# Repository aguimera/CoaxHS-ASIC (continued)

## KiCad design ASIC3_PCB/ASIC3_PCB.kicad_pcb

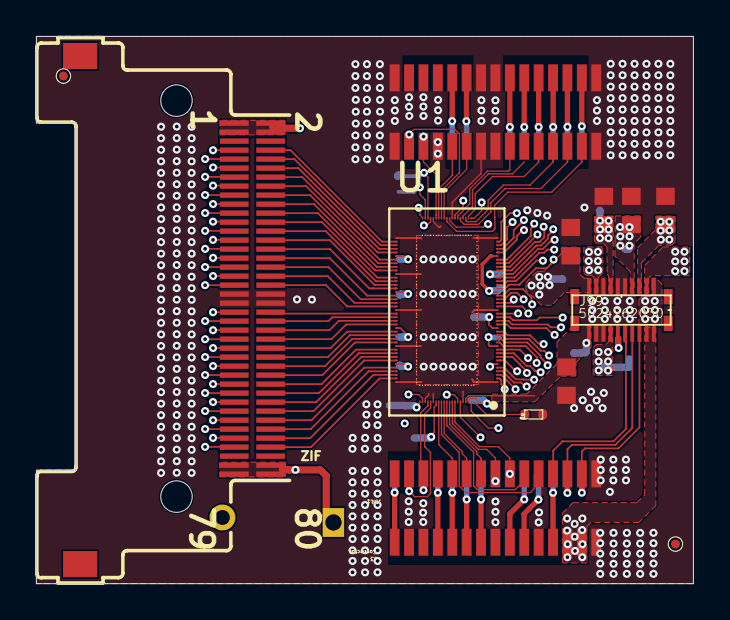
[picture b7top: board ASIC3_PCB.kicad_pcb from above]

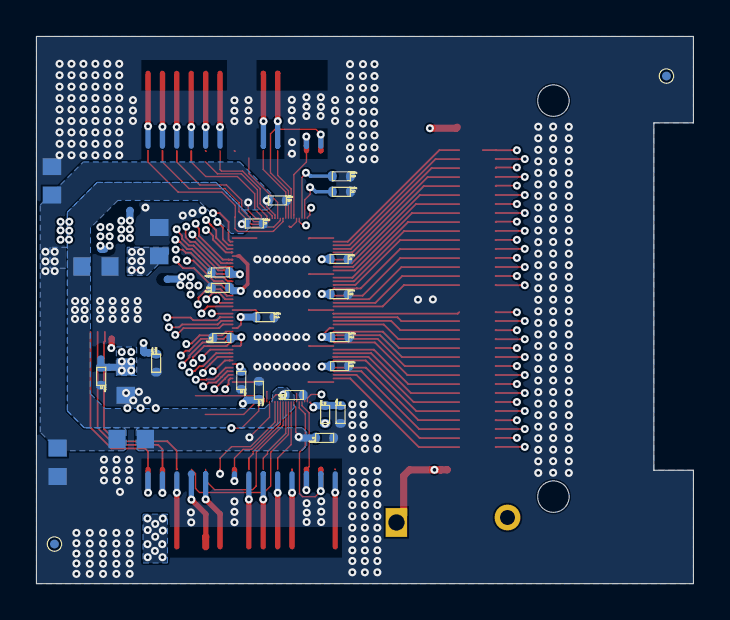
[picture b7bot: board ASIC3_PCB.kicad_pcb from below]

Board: 6 copper layers, 36.5 x 30.4 mm, 42 parts (28 on the bottom side), 101 nets.

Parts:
C1, C2, C4, C5, C6, C7, C8, C9, C10, C11, C12, C13, C14, C17, C18, C19, C400, C401, C402: 100n; C0402
C200, C201, C202, C203, C204, C205, C206, C207, C208, C209: 10uF; CAPC1709X50N
FF1: 0F0; CAPC1709X50N
FID1, FID2, FID3, FID4: FIDUCIAL; MFID0508
J3: Connector; JSIL1THTPad
J6: MOLEX-524653071; J524653071_Board2Board
J11: MEC5-040-01-L-RA-W2-TR
J99: 5024262030; JMOLEX-0559090274V1_pwrcard
J200: MOLEX-524653071; J524653071
R2: 0R0; R0402
R3: 33k; R0402
U1: ASIC3_M; BRAINCOM_ASIC3

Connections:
4V5: J99.2, J99.4, J200.28, J200.29
/Col_0: J11.73 (Col_0), U1.2 (2_VOUT_COL_Q_170)
/Col_1: J11.71 (Col_1), U1.3 (3_VOUT_COL_I_170)
/Col_2: J11.69 (Col_2), U1.4 (4_VOUT_COL_I_180)
/Col_3: J11.67 (Col_3), U1.5 (5_VOUT_COL_Q_180)
/Col_4: J11.65 (Col_4), U1.7 (7_VOUT_COL_Q_190)
/Col_5: J11.63 (Col_5), U1.8 (8_VOUT_COL_I_190)
/Col_6: J11.61 (Col_6), U1.9 (9_VOUT_COL_I_200)
/Col_7: J11.59 (Col_7), U1.10 (10_VOUT_COL_Q_200)
/Col_8: J11.57 (Col_8), U1.12 (12_VOUT_COL_Q_210)
/Col_9: J11.55 (Col_9), U1.13 (13_VOUT_COL_I_210)
/Col_10: J11.53 (Col_10), U1.14 (14_VOUT_COL_I_220)
/Col_11: J11.51 (Col_11), U1.15 (15_VOUT_COL_Q_220)
/Col_12: J11.49 (Col_12), U1.17 (17_VOUT_COL_Q_230)
/Col_13: J11.47 (Col_13), U1.18 (18_VOUT_COL_I_230)
/Col_14: J11.45 (Col_14), U1.19 (19_VOUT_COL_I_240)
/Col_15: J11.43 (Col_15), U1.20 (20_VOUT_COL_Q_240)
/Col_16: J11.37 (Col_16), U1.22 (22_VOUT_COL_Q_250)
/Col_17: J11.35 (Col_17), U1.23 (23_VOUT_COL_I_250)
/Col_18: J11.33 (Col_18), U1.24 (24_VOUT_COL_I_260)
/Col_19: J11.31 (Col_19), U1.25 (25_VOUT_COL_Q_260)
/Col_20: J11.29 (Col_20), U1.27 (27_VOUT_COL_Q_270)
/Col_21: J11.27 (Col_21), U1.28 (28_VOUT_COL_I_270)
/Col_22: J11.25 (Col_22), U1.29 (29_VOUT_COL_I_280)
/Col_23: J11.23 (Col_23), U1.30 (30_VOUT_COL_Q_280)
/Col_24: J11.21 (Col_24), U1.32 (32_VOUT_COL_Q_290)
/Col_25: J11.19 (Col_25), U1.33 (33_VOUT_COL_I_290)
/Col_26: J11.17 (Col_26), U1.34 (34_VOUT_COL_I_300)
/Col_27: J11.15 (Col_27), U1.35 (35_VOUT_COL_Q_300)
/Col_28: J11.13 (Col_28), U1.37 (37_VOUT_COL_Q_310)
/Col_29: J11.11 (Col_29), U1.38 (38_VOUT_COL_I_310)
/Col_30: J11.9 (Col_30), U1.39 (39_VOUT_COL_I_320)
/Col_31: J11.7 (Col_31), U1.40 (40_VOUT_COL_Q_320)
/DAC_SCK: J99.8, J200.3
/DAC_SDI: J99.6, J200.2
/M0_B: J200.14, U1.106 (106_M0_B)
/M1_B: J200.13, U1.105 (105_M1_B)
/MODE_0: J6.21, U1.52 (52_MODE_0)
/MODE_1: J6.29, U1.51 (51_MODE_1)
/OSC_CLK: J200.7, U1.115 (115_OSC_CLK)
/Row_0: J11.74 (Row_0), U1.100 (100_I_IN_F_0_B_0)
/Row_1: J11.72 (Row_1), U1.99 (99_I_IN_F_1_B_0)
/Row_2: J11.70 (Row_2), U1.98 (98_I_IN_F_2_B_0)
/Row_3: J11.68 (Row_3), U1.97 (97_I_IN_F_3_B_0)
/Row_4: J11.66 (Row_4), U1.95 (95_I_IN_F_0_B_1)
/Row_5: J11.64 (Row_5), U1.94 (94_I_IN_F_1_B_1)
/Row_6: J11.62 (Row_6), U1.93 (93_I_IN_F_2_B_1)
/Row_7: J11.60 (Row_7), U1.92 (92_I_IN_F_3_B_1)
/Row_8: J11.58 (Row_8), U1.90 (90_I_IN_F_0_B_2)
/Row_9: J11.56 (Row_9), U1.89 (89_I_IN_F_1_B_2)
/Row_10: J11.54 (Row_10), U1.88 (88_I_IN_F_2_B_2)
/Row_11: J11.52 (Row_11), U1.87 (87_I_IN_F_3_B_2)
/Row_12: J11.50 (Row_12), U1.85 (85_I_IN_F_0_B_3)
/Row_13: J11.48 (Row_13), U1.84 (84_I_IN_F_1_B_3)
/Row_14: J11.46 (Row_14), U1.83 (83_I_IN_F_2_B_3)
/Row_15: J11.44 (Row_15), U1.82 (82_I_IN_F_3_B_3)
/Row_16: J11.38 (Row_16), U1.80 (80_I_IN_F_0_B_4)
/Row_17: J11.36 (Row_17), U1.79 (79_I_IN_F_1_B_4)
/Row_18: J11.34 (Row_18), U1.78 (78_I_IN_F_2_B_4)
/Row_19: J11.32 (Row_19), U1.77 (77_I_IN_F_3_B_4)
/Row_20: J11.30 (Row_20), U1.75 (75_I_IN_F_0_B_5)
/Row_21: J11.28 (Row_21), U1.74 (74_I_IN_F_1_B_5)
/Row_22: J11.26 (Row_22), U1.73 (73_I_IN_F_2_B_5)
/Row_23: J11.24 (Row_23), U1.72 (72_I_IN_F_3_B_5)
/Row_24: J11.22 (Row_24), U1.70 (70_I_IN_F_0_B_6)
/Row_25: J11.20 (Row_25), U1.69 (69_I_IN_F_1_B_6)
/Row_26: J11.18 (Row_26), U1.68 (68_I_IN_F_2_B_6)
/Row_27: J11.16 (Row_27), U1.67 (67_I_IN_F_3_B_6)
/Row_28: J11.14 (Row_28), U1.65 (65_I_IN_F_0_B_7)
/Row_29: J11.12 (Row_29), U1.64 (64_I_IN_F_1_B_7)
/Row_30: J11.10 (Row_30), U1.63 (63_I_IN_F_2_B_7)
/Row_31: J11.8 (Row_31), U1.62 (62_I_IN_F_3_B_7)
/SCLK: J200.8, U1.114 (114_SCLK)
/SER_B0: J200.5, U1.110 (110_SER_B0)
/SER_B1: J200.10, U1.111 (111_SER_B1)
/SER_B2: J200.6, U1.112 (112_SER_B2)
/SER_B3: J200.9, U1.113 (113_SER_B3)
/SER_B4: J6.26, U1.43 (43_SER_B4)
/SER_B5: J6.27, U1.44 (44_SER_B5)
/SER_B6: J6.25, U1.45 (45_SER_B6)
/SER_B7: J6.28, U1.46 (46_SER_B7)
/SER_CLK_0: J200.11, U1.109 (109_GND)
/SER_CLK_1: J6.24, U1.47 (47_SER_CLK_1)
/SPI_CLK: J6.17, U1.53 (53_SPI_CLK)
/SPI_DATA: J6.18, U1.55 (55_SPI_DATA)
/\DAC_CS: J99.10, J200.4
/\SPI_CS: J6.20, U1.54 (54_SPI_CS)
BATH: J3.1, J11.1 (Bath), J11.2 (Bath), J11.3 (Bath), J11.4 (Bath), J11.77 (Bath), J11.78 (Bath), J11.79 (Bath), J11.80 (Bath), J99.12
G: C1.2, C2.1, C4.2, C5.1, C6.1, C7.1, C8.1, C9.1, C10.1, C11.1, C12.1, C13.1, C14.1, C17.1, C18.1, C19.1, C200.2, C201.2, C202.2, C203.2, C204.2, C205.2, C206.2, C207.2, C208.2, C209.2, C400.2, C401.2, C402.2, J6.1, J6.8, J6.9, J6.15, J6.16, J6.19, J6.22, J6.23, J6.30, J11.39 (GND), J11.40 (GND), J11.41 (GND), J11.42 (GND), J99.9, J99.11, J99.15, J99.16, J99.18, J200.1, J200.30, R3.2, U1.1 (1GND), U1.21 (21_GND), U1.41 (41_GND), U1.49 (49_GND), U1.56 (56_GND), U1.61 (61_GND), U1.71 (71_GND), U1.81 (81_GND), U1.91 (91_GND), U1.101 (101_GND), U1.104 (104_GND), U1.107 (107_GND), U1.118 (118_GND)
unnamed: C4.1, R2.1, U1.102 (102_VCM)
unnamed: C1.1, FF1.2, U1.108 (108_VDD_D), U1.117 (117_VDD_D)
unnamed: R3.1, U1.122 (122_V_RES_IN)
VCM: C5.2, C11.2, C14.2, C202.1, J99.17, R2.2, U1.6 (6_VCM), U1.16 (16_VCM), U1.26 (26_VCM), U1.36 (36_VCM), U1.60 (60_VCM)
VDD_A: C6.2, C7.2, C8.2, C10.2, C12.2, C13.2, C200.1, J99.19, U1.11 (11_VDD_A), U1.31 (31_VDD_A), U1.57 (57_VDD_A), U1.66 (66_VDD_A), U1.76 (76_VDD_A), U1.86 (86_VDD_A), U1.96 (96_VDD_A), U1.103 (103_VDD_A)
VDD_D: C18.2, C201.1, C208.1, FF1.1, J99.3, U1.42 (42_VDD_D), U1.48 (48_VDD_D)
VDD_D_1V2: C9.2, C209.1, C400.1, J99.1, U1.50 (50_VDD_D_1V2), U1.116 (116_VDD_D_1V2)
VREF_C: C2.2, C203.1, J99.14, U1.121 (121_V_REF_C)
VREF_H: C17.2, C204.1, J99.7, U1.59 (59_VREF_SH)
VREF_H_L: C206.1, C401.1, J99.13, U1.120 (120_V_REF_H)
VREF_L: C19.2, C207.1, J99.5, U1.58 (58_VREF_SL)
VREF_L_L: C205.1, C402.1, J99.20, U1.119 (119_VREF_L)

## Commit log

2023-11-29 First comit
2023-11-29 Backlink to CADLAB.io has been added.
2023-11-29 remove bottom connector to second ASIC
2023-11-30 Add all PCBs
2023-12-14 Add ASIC test layer
2023-12-14 add libs
2023-12-14 fixed test layer
2023-12-14 Add datasheets
2024-03-08 Test Commint
2024-03-08 add gitignore
2024-03-08 Test_layer2
2024-03-12 Ser_to_ASIC
2024-03-15 inici placa
2024-03-22 actualitzacio
2024-04-02 canvis
